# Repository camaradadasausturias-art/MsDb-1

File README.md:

Hey there, fellow human!
I'm a portuguese 17 year old highschooler with aspirations of getting into aerospacial engineering one day. And since I know how important it is to start building experience
early, I decided to try out a hackclub starter project. And what an undertaking this was. I picked the "Design a custom PCB" thinking it couldnt be THAT hard. Yeah
no, hard would be the understatement of the century. I had hardly ever touched a CAD program in my life, and KiCAD looked like it'd have a very sharp looking skill curve.
As it did indeed. But I presevered. Despite me relentlessly complaining about you guys' tutorial, I have to admit it was essential to me completing this, and it sure forced me
to learn a lot at times when it did not hold my hand through some of the ins and outs of PCB building. I love every bit that led me to completing my first ever PCB,
hopefully of more to come!

I'm also not particularily handy with GitHub, I've honestly always found the UI to be quite intimidating. I think I satisfy your admission requirements, but I wouldnt put it above me to miss something fulcral completely. 

The board is named after my own versioning system. Ms are my initials, Db stands for DevBoard, the first 1 is the major version count, the A is the major branch count, and the final number is the revision count.

I spent way longer than anticipated, partly due to some complications that occured while trying to find the smaller flash storage and LDO that the tutorial used, that led me to quite the quagmire in trying to fit much larger components in a board with nearly the same footprint. Though that led me to a design that implemented a whoping 16MB of flash storage, some 8x more than the Raspberry Pi Pico. And an LDO capable of drawing more current. So yeah here's that as a unique factor LOL.

ChatGPT did me a solid on this one. If you're interested in seeing an LLM teach the equivalent of a foulmouthed juvenile chimpanzee how PCB's work, here's our full conversation: https://chatgpt.com/share/69e56555-d1f8-83eb-b878-137e63521a72
And don't worry, the most "AI" that was actually _directly_ inolved in the making of this project was the DRC rules checker. 

Anyhow, here's some eye candy for your troubles of  reading this:

And here's the BOM from the website:
[BOM MsDb-1A3-JLCPCB Assembly Order (1).csv](https://github.com/user-attachments/files/26879597/BOM.MsDb-1A3-JLCPCB.Assembly.Order.1.csv)

Have a good one reviewing! My journal features a couple particularily humourous entries.

Update: fixed a capacitor footprint mismatch issue. Version 1A3 is the most current one, ready for review. Note that some files may or may not be mistakenly named as MsCp-XXX.

Update 2: Im really sorry for the mess this repository is. This UI is completely new to me, and I cant find the way to get all the files where I want them. When in doubt, always consult the latest versions.

-----------------------------------------------------------------------------------------------------------------
IMPORTANT:

Update 3: Looking back, I can see that some of my wording contrasts quite sharply with my actual broader feelings for hackclub's cause, so I feel the need to clarify a bit.

I believe I should have kept it a bit more mature in the journal. Though it was humourous to read some of the entries I had left, many were made the way they were for exactly the purpose of being funny, something which I honestly regard as a mistake. Some things were taken out of proportion in a place where I feel like things should have been a bit more grounded, and especially for a reviewer who does not know me at all, I see how they might be taken as me not taking the project seriously. I took the generally casual wording of your website and ran with it way too far. My mistake for that.

For being a complexity 2 project, the tutorial likely assumed some previous experience in the field, something which I, who simply picked the most interesting starter project regardless of complexity, failed to account for.
Hence the need for so many explanations, hence the frustration. And, considering my exaustion for working non stop for days, the chaotic formatting and tone. 

I'm writing this now in a much clearer headspace, and while I am not exactly catastrophizing this, I do feel like I didn't pay the respect I should have, especially to the tutorial, and that deserves an apology. 

ChaGPT acted here as a consultant, which is another point I'd like to emphasize, because I did convey this rather badly both in the journal and in my previous paragraph. What I meant by it not being "directly involved" was specifically it not being a direct agent or a decision-taker, having served solely for the purpose of research, counseling, and honestly venting. The way I framed it against the DRC was wrong, as they actually both served similar purposes, to sanity check. 

Also, me thinking the project could be counted as tier 3 was a bit silly. Me being new to this and having struggled with it doesnt warrant a higher complexity rating. 

I hope the last entry I submitted in the journal at the time of sumbittal now sounds a bit less out of character. Truth is that it is my character, and my level-headed feelings toward the organization. Something which I had previously failed to convey amidst my frustration and my desire to be funny to myself.

That said, while I do regret a couple things, I'll take it in stride and strive to be better. You live and you learn, and I can safely say that this was a huge learning experience, both in KiCAD and in how I should address things in records. 

Have a good day, and thank you for the work you're putting in for this foundation.

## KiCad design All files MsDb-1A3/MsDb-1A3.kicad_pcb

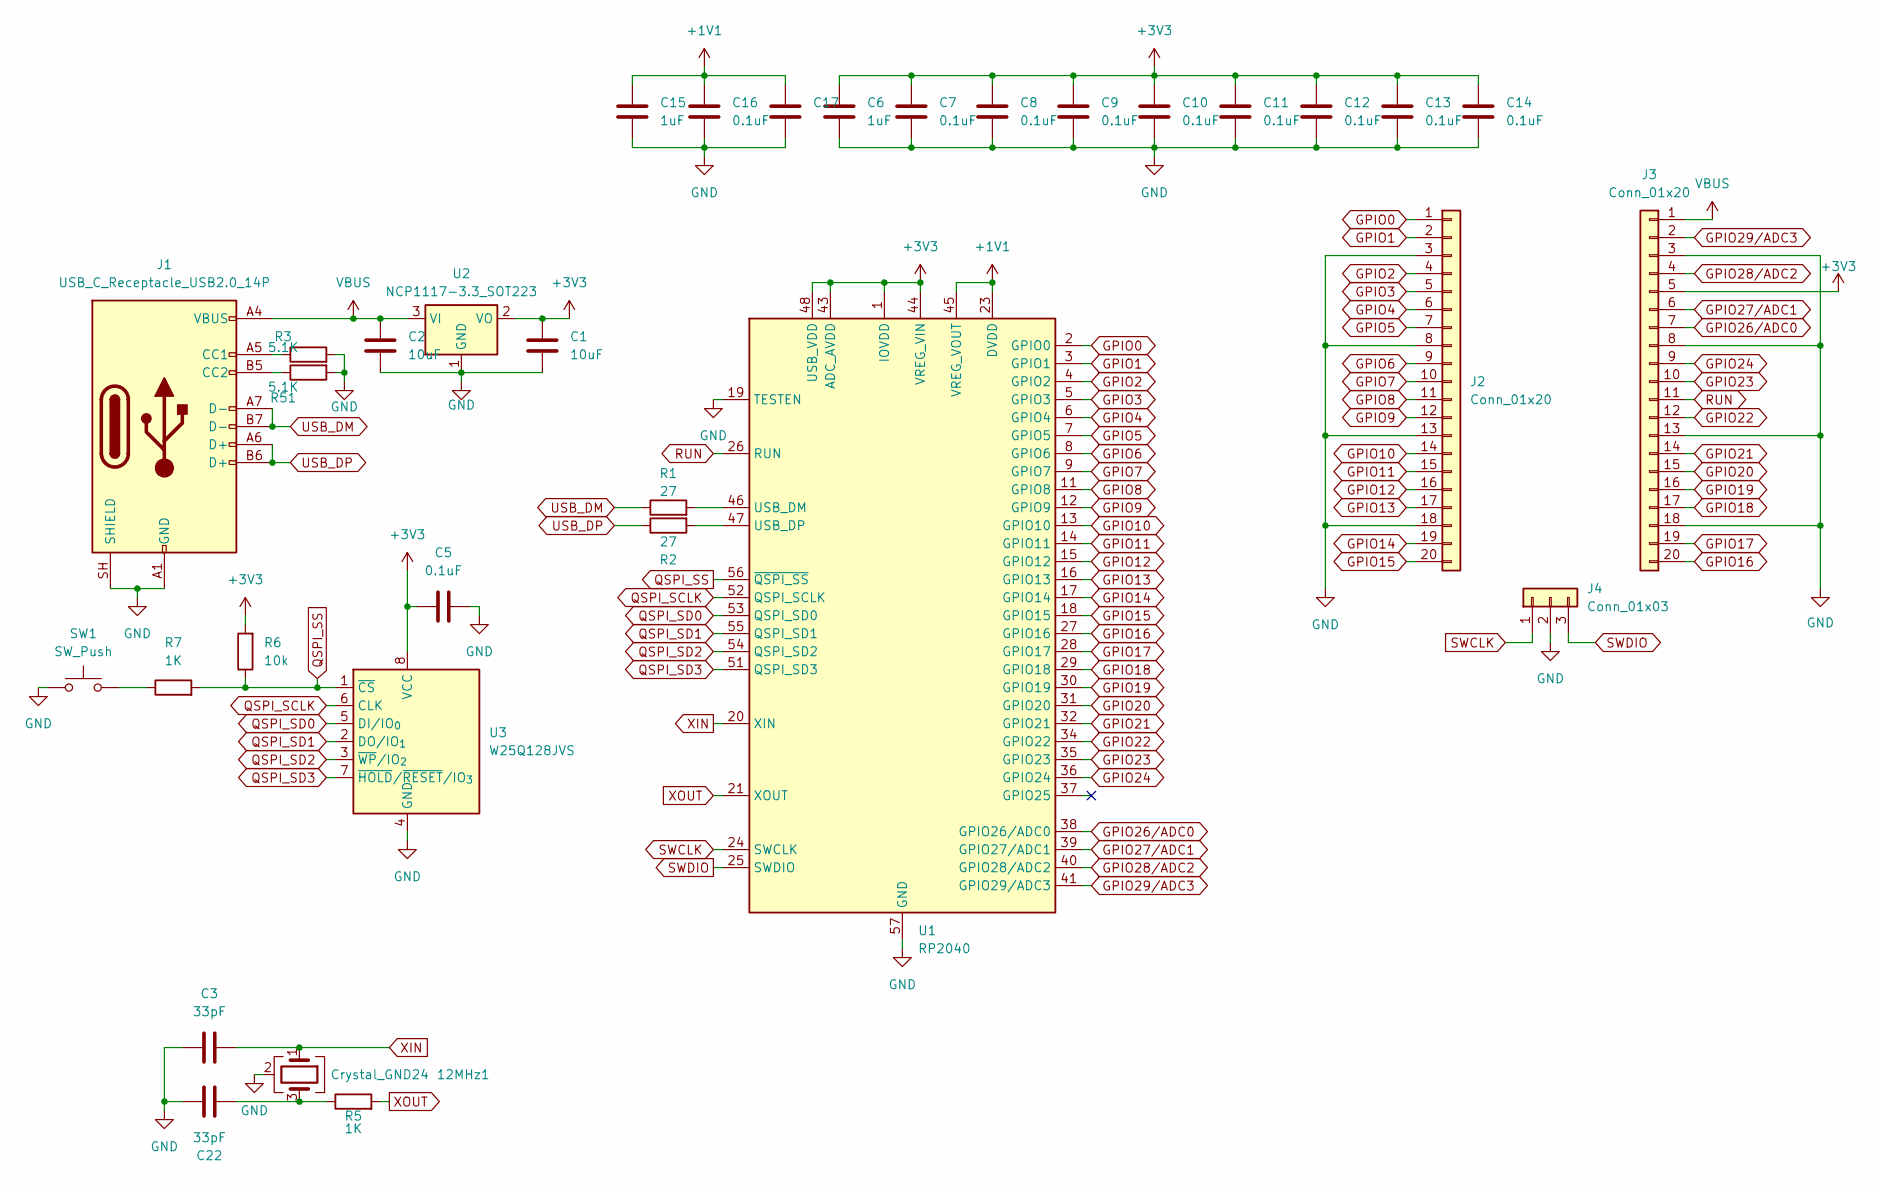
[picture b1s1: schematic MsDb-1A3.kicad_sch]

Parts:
12MHz1: Crystal_GND24; Crystal_SMD_3225-4Pin_3.2x2.5mm
C1, C2: 10uF; C_0603_1608Metric
C3, C22: 33pF; C_0402_1005Metric_Pad0.74x0.62mm_HandSolder
C5, C7, C8, C9, C10, C11, C12, C13, C14, C16, C17: 0.1uF; C_0402_1005Metric_Pad0.74x0.62mm_HandSolder
C6, C15: 1uF; C_0402_1005Metric_Pad0.74x0.62mm_HandSolder
J1: USB_C_Receptacle_USB2.0_14P; USB_C_Receptacle_HRO_TYPE-C-31-M-12
J2, J3: Conn_01x20; PinHeader_1x20_P2.54mm_Vertical
J4: Conn_01x03; PinHeader_1x03_P2.54mm_Vertical
R1, R2: 27; R_0402_1005Metric
R3: 5.1K; R_0402_1005Metric
R5, R7: 1K; R_0402_1005Metric
R6: 10k; R_0402_1005Metric
R51: 5.1K; R_0402_1005Metric_Pad0.72x0.64mm_HandSolder
SW1: SW_Push; SW_SPST_TS-1088-xR020
U1: RP2040; QFN-56-1EP_7x7mm_P0.4mm_EP3.2x3.2mm
U2: NCP1117-3.3_SOT223; SOT-223-3_TabPin2
U3: W25Q128JVS; SOIC-8_5.3x5.3mm_P1.27mm

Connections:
+1V1: C15.1, C16.1, C17.1, U1.23 (DVDD), U1.45 (VREG_VOUT), U1.50 (DVDD)
+3V3: C1.1, C5.1, C6.1, C7.1, C8.1, C9.1, C10.1, C11.1, C12.1, C13.1, C14.1, J3.5, R6.2, U1.1 (IOVDD), U1.10 (IOVDD), U1.22 (IOVDD), U1.33 (IOVDD), U1.42 (IOVDD), U1.43 (ADC_AVDD), U1.44 (VREG_VIN), U1.48 (USB_VDD), U1.49 (IOVDD), U2.2 (VO), U3.8 (VCC); also elsewhere on the board
GND: 12MHz1.2 (G), 12MHz1.4 (G), C1.2, C2.2, C3.2, C5.2, C6.2, C7.2, C8.2, C9.2, C10.2, C11.2, C12.2, C13.2, C14.2, C15.2, C16.2, C17.2, C22.1, J1.A1 (GND), J1.A12 (GND), J1.B1 (GND), J1.B12 (GND), J1.SH (SHIELD), J2.3, J2.8, J2.13, J2.18, J3.3, J3.8, J3.13, J3.18, J4.2, R3.2, R51.2, SW1.1, U1.19 (TESTEN), U1.57 (GND), U2.1 (GND), U3.4 (GND); also elsewhere on the board
GPIO0: J2.1, U1.2 (GPIO0)
GPIO1: J2.2, U1.3 (GPIO1)
GPIO2: J2.4, U1.4 (GPIO2)
GPIO3: J2.5, U1.5 (GPIO3)
GPIO4: J2.6, U1.6 (GPIO4)
GPIO5: J2.7, U1.7 (GPIO5)
GPIO6: J2.9, U1.8 (GPIO6)
GPIO7: J2.10, U1.9 (GPIO7)
GPIO8: J2.11, U1.11 (GPIO8)
GPIO9: J2.12, U1.12 (GPIO9)
GPIO10: J2.14, U1.13 (GPIO10)
GPIO11: J2.15, U1.14 (GPIO11)
GPIO12: J2.16, U1.15 (GPIO12)
GPIO13: J2.17, U1.16 (GPIO13)
GPIO14: J2.19, U1.17 (GPIO14)
GPIO15: J2.20, U1.18 (GPIO15)
GPIO16: J3.20, U1.27 (GPIO16); also elsewhere on the board
GPIO17: J3.19, U1.28 (GPIO17); also elsewhere on the board
GPIO18: J3.17, U1.29 (GPIO18); also elsewhere on the board
GPIO19: J3.16, U1.30 (GPIO19); also elsewhere on the board
GPIO20: J3.15, U1.31 (GPIO20); also elsewhere on the board
GPIO21: J3.14, U1.32 (GPIO21); also elsewhere on the board
GPIO22: J3.12, U1.34 (GPIO22); also elsewhere on the board
GPIO23: J3.10, U1.35 (GPIO23); also elsewhere on the board
GPIO24: J3.9, U1.36 (GPIO24); also elsewhere on the board
GPIO26/ADC0: J3.7, U1.38 (GPIO26/ADC0); also elsewhere on the board
GPIO27/ADC1: J3.6, U1.39 (GPIO27/ADC1); also elsewhere on the board
GPIO28/ADC2: J3.4, U1.40 (GPIO28/ADC2); also elsewhere on the board
GPIO29/ADC3: J3.2, U1.41 (GPIO29/ADC3); also elsewhere on the board
unnamed 32: 12MHz1.3, C22.2, R5.1; also elsewhere on the board
unnamed: J1.A5 (CC1), R3.1
unnamed: J1.B5 (CC2), R51.1
unnamed: R7.1, SW1.2
unnamed: R1.2, U1.46 (USB_DM)
unnamed: R2.2, U1.47 (USB_DP)
QSPI_SCLK: U1.52 (QSPI_SCLK), U3.6 (CLK)
QSPI_SD0: U1.53 (QSPI_SD0), U3.5 (DI/IO_{0})
QSPI_SD1: U1.55 (QSPI_SD1), U3.2 (DO/IO_{1})
QSPI_SD2: U1.54 (QSPI_SD2), U3.3 (~WP/IO_{2})
QSPI_SD3: U1.51 (QSPI_SD3), U3.7 (~HOLD/~RESET/IO_{3})
QSPI_SS: R6.1, R7.2, U1.56 (~QSPI_SS), U3.1 (~CS)
RUN: J3.11, U1.26 (RUN); also elsewhere on the board
SWCLK: J4.1, U1.24 (SWCLK)
SWDIO: J4.3, U1.25 (SWDIO)
USB_D+: J1.A6 (D+), J1.B6 (D+), R2.1
USB_D-: J1.A7 (D-), J1.B7 (D-), R1.1
VBUS: C2.1, J1.A4 (VBUS), J1.A9 (VBUS), J1.B4 (VBUS), J1.B9 (VBUS), J3.1, U2.3 (VI); also elsewhere on the board
XIN: 12MHz1.1, C3.1, U1.20 (XIN); also elsewhere on the board
XOUT: R5.2, U1.21 (XOUT)

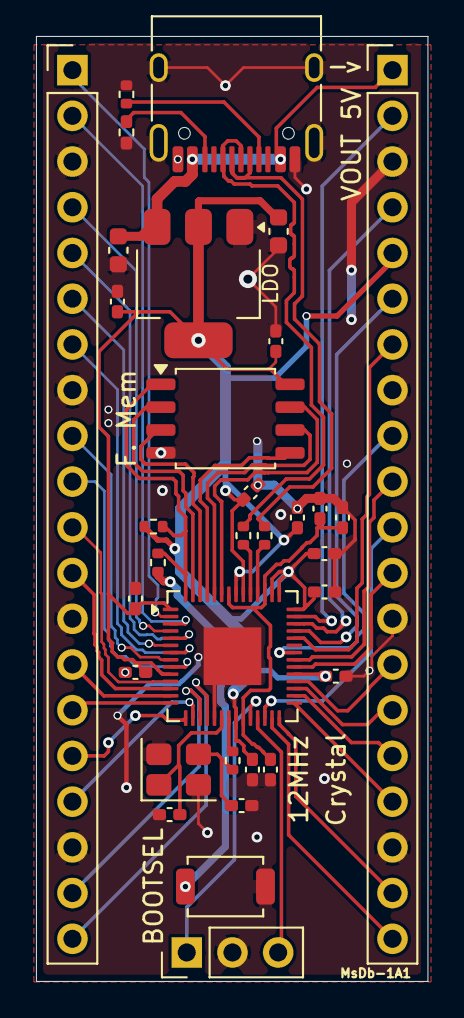
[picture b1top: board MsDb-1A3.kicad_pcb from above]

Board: 2 copper layers, 21.8 x 52.5 mm, 33 parts (0 on the bottom side), 52 nets.

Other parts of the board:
Crystal_GND24: 12MHz; Crystal_SMD_3225-4Pin_3.2x2.5mm
VOUT 5V v: Conn_01x20; PinHeader_1x20_P2.54mm_Vertical

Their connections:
+3V3: VOUT 5V v.5; also elsewhere on the board
GND: Crystal_GND24.2 (G), Crystal_GND24.4 (G), VOUT 5V v.3, VOUT 5V v.8, VOUT 5V v.13, VOUT 5V v.18; also elsewhere on the board
GPIO16: VOUT 5V v.20; also elsewhere on the board
GPIO17: VOUT 5V v.19; also elsewhere on the board
GPIO18: VOUT 5V v.17; also elsewhere on the board
GPIO19: VOUT 5V v.16; also elsewhere on the board
GPIO20: VOUT 5V v.15; also elsewhere on the board
GPIO21: VOUT 5V v.14; also elsewhere on the board
GPIO22: VOUT 5V v.12; also elsewhere on the board
GPIO23: VOUT 5V v.10; also elsewhere on the board
GPIO24: VOUT 5V v.9; also elsewhere on the board
GPIO26/ADC0: VOUT 5V v.7; also elsewhere on the board
GPIO27/ADC1: VOUT 5V v.6; also elsewhere on the board
GPIO28/ADC2: VOUT 5V v.4; also elsewhere on the board
GPIO29/ADC3: VOUT 5V v.2; also elsewhere on the board
unnamed 32: Crystal_GND24.3; also elsewhere on the board
RUN: VOUT 5V v.11; also elsewhere on the board
VBUS: VOUT 5V v.1; also elsewhere on the board
XIN: Crystal_GND24.1; also elsewhere on the board

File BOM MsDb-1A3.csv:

Id,Designator,Footprint,Quantity,Comment,Supplier and ref
1,Y1,Crystal:Crystal_SMD_3225-4Pin_3.2x2.5mm,1,12MHz1,
2,C1,Capacitor_SMD:C_0201_0603Metric_Pad0.64x0.40mm_HandSolder,1,10uF,
3,C2,Capacitor_SMD:C_0201_0603Metric_Pad0.64x0.40mm_HandSolder,1,10uF,
4,C3,Capacitor_SMD:C_0402_1005Metric_Pad0.74x0.62mm_HandSolder,1,33pF,
5,C5,Capacitor_SMD:C_0402_1005Metric_Pad0.74x0.62mm_HandSolder,1,0.1uF,
6,C6,Capacitor_SMD:C_0402_1005Metric_Pad0.74x0.62mm_HandSolder,1,1uF,
7,C7,Capacitor_SMD:C_0402_1005Metric_Pad0.74x0.62mm_HandSolder,1,0.1uF,
8,C8,Capacitor_SMD:C_0402_1005Metric_Pad0.74x0.62mm_HandSolder,1,0.1uF,
9,C9,Capacitor_SMD:C_0402_1005Metric_Pad0.74x0.62mm_HandSolder,1,0.1uF,
10,C10,Capacitor_SMD:C_0402_1005Metric_Pad0.74x0.62mm_HandSolder,1,0.1uF,
11,C11,Capacitor_SMD:C_0402_1005Metric_Pad0.74x0.62mm_HandSolder,1,0.1uF,
12,C12,Capacitor_SMD:C_0402_1005Metric_Pad0.74x0.62mm_HandSolder,1,0.1uF,
13,C13,Capacitor_SMD:C_0402_1005Metric_Pad0.74x0.62mm_HandSolder,1,0.1uF,
14,C14,Capacitor_SMD:C_0402_1005Metric_Pad0.74x0.62mm_HandSolder,1,0.1uF,
15,C15,Capacitor_SMD:C_0402_1005Metric_Pad0.74x0.62mm_HandSolder,1,1uF,
16,C16,Capacitor_SMD:C_0402_1005Metric_Pad0.74x0.62mm_HandSolder,1,0.1uF,
17,C17,Capacitor_SMD:C_0402_1005Metric_Pad0.74x0.62mm_HandSolder,1,0.1uF,
18,C22,Capacitor_SMD:C_0402_1005Metric_Pad0.74x0.62mm_HandSolder,1,33pF,
19,J1,Connector_USB:USB_C_Receptacle_HRO_TYPE-C-31-M-12,1,USB_C_Receptacle_USB2.0_14P,
20,J2,Connector_PinHeader_2.54mm:PinHeader_1x20_P2.54mm_Vertical,1,Conn_01x20,
21,J3,Connector_PinHeader_2.54mm:PinHeader_1x20_P2.54mm_Vertical,1,Conn_01x20,
22,J4,Connector_PinHeader_2.54mm:PinHeader_1x03_P2.54mm_Vertical,1,Conn_01x03,
23,R1,Resistor_SMD:R_0402_1005Metric,1,27,
24,R2,Resistor_SMD:R_0402_1005Metric,1,27,
25,R3,Resistor_SMD:R_0402_1005Metric,1,5.1K,
26,R5,Resistor_SMD:R_0402_1005Metric,1,1K,
27,R6,Resistor_SMD:R_0402_1005Metric,1,10k,
28,R7,Resistor_SMD:R_0402_1005Metric,1,1K,
29,R51,Resistor_SMD:R_0402_1005Metric_Pad0.72x0.64mm_HandSolder,1,5.1K,
30,SW1,Button_Switch_SMD:SW_SPST_TS-1088-xR020,1,SW_Push,
31,U1,Package_DFN_QFN:QFN-56-1EP_7x7mm_P0.4mm_EP3.2x3.2mm,1,RP2040,
32,U2,Package_TO_SOT_SMD:SOT-223-3_TabPin2,1,NCP1117-3.3_SOT223,
33,U3,Package_SO:SOIC-8_5.3x5.3mm_P1.27mm,1,W25Q128JVS,

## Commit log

2026-04-19 Add README
    Added a detailed project description, including background, challenges faced, and a bill of materials (BOM).
2026-04-19 Add ChatGPT conversation link to README
    Updated the README to include a link to a conversation with ChatGPT about PCB design.
2026-04-20 Fix capacitor footprint mismatch in README
    Updated capacitor footprint for C1 and C2 in the BOM.
2026-04-20 Revise BOM details and fix footprint mismatch
    Added links to relevant files and clarified repository organization.
2026-04-20 Update README with BOM changes and repository notes
    Removed outdated BOM details and added updates regarding capacitor footprint issues and repository organization.
2026-04-20 Delete BOM MsDb-1A3.csv
    It's simply wrong
2026-04-21 Revise README for tone clarification and apologies
    Clarified previous statements regarding project complexity and personal reflections. Apologized for tone and formatting issues in the journal entries.
2026-04-24 Add new image and remove an old image in README
